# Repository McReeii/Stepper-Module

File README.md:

# Stepper-Module
 Smart_Stepper_Module

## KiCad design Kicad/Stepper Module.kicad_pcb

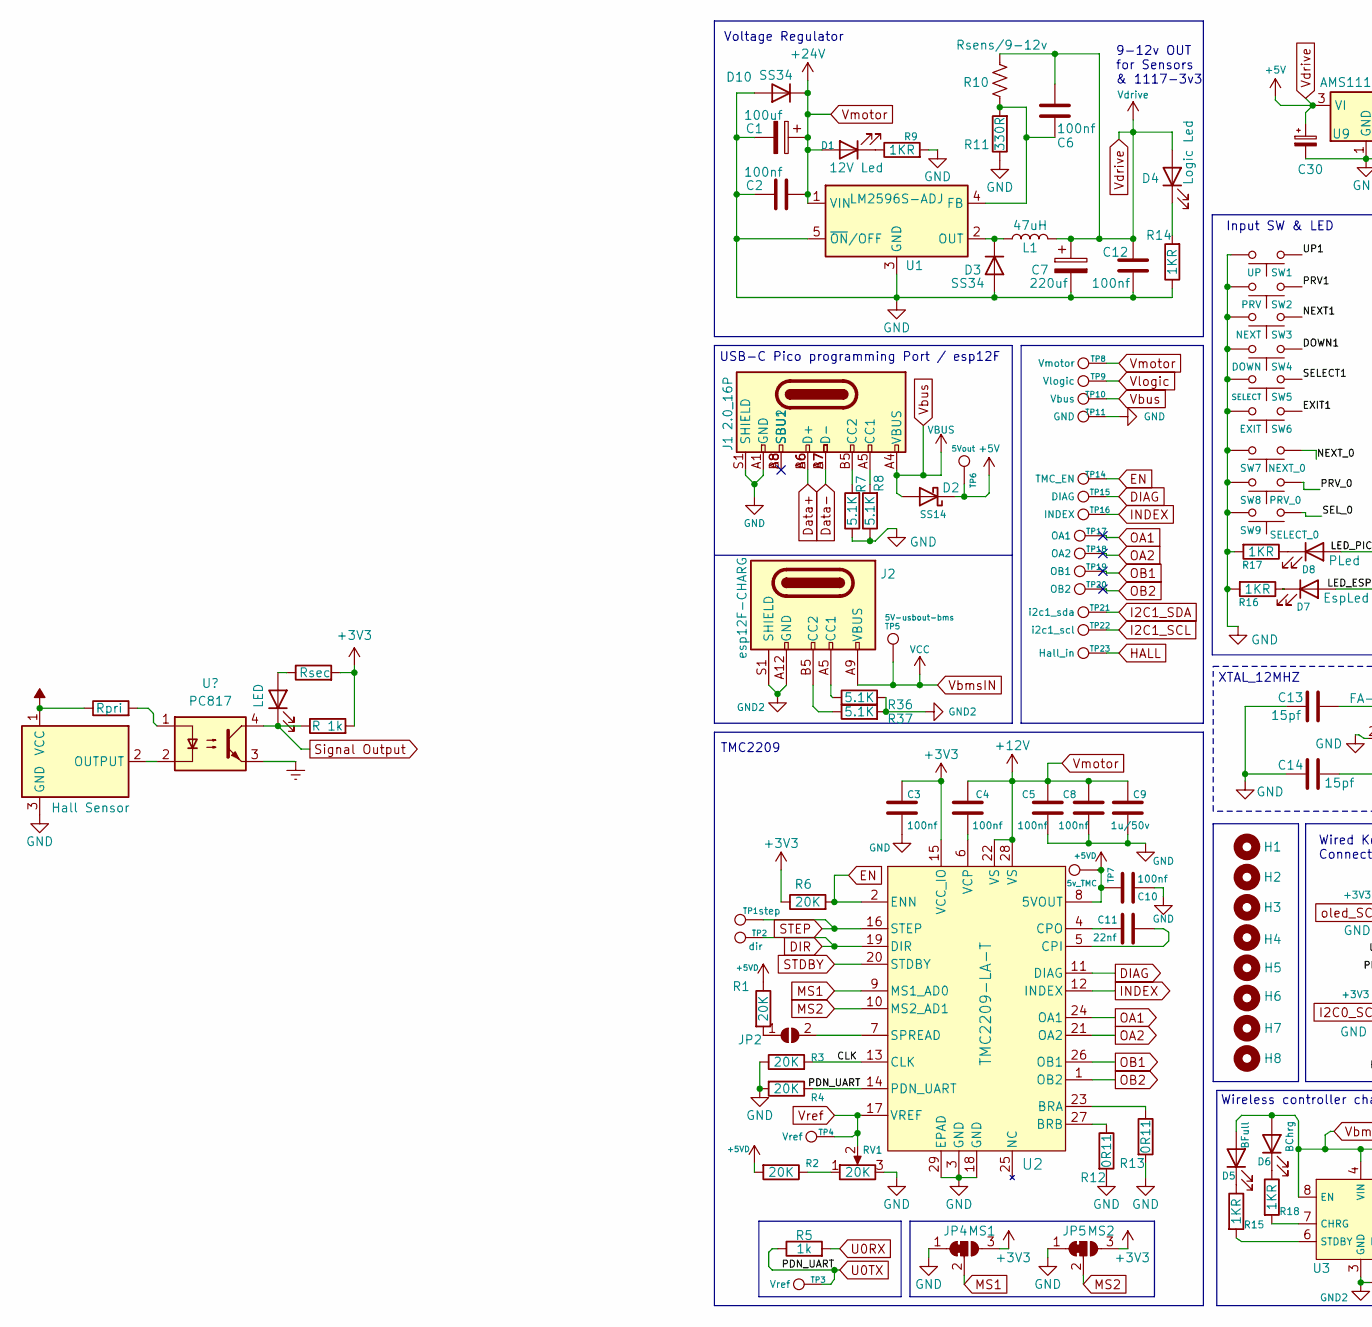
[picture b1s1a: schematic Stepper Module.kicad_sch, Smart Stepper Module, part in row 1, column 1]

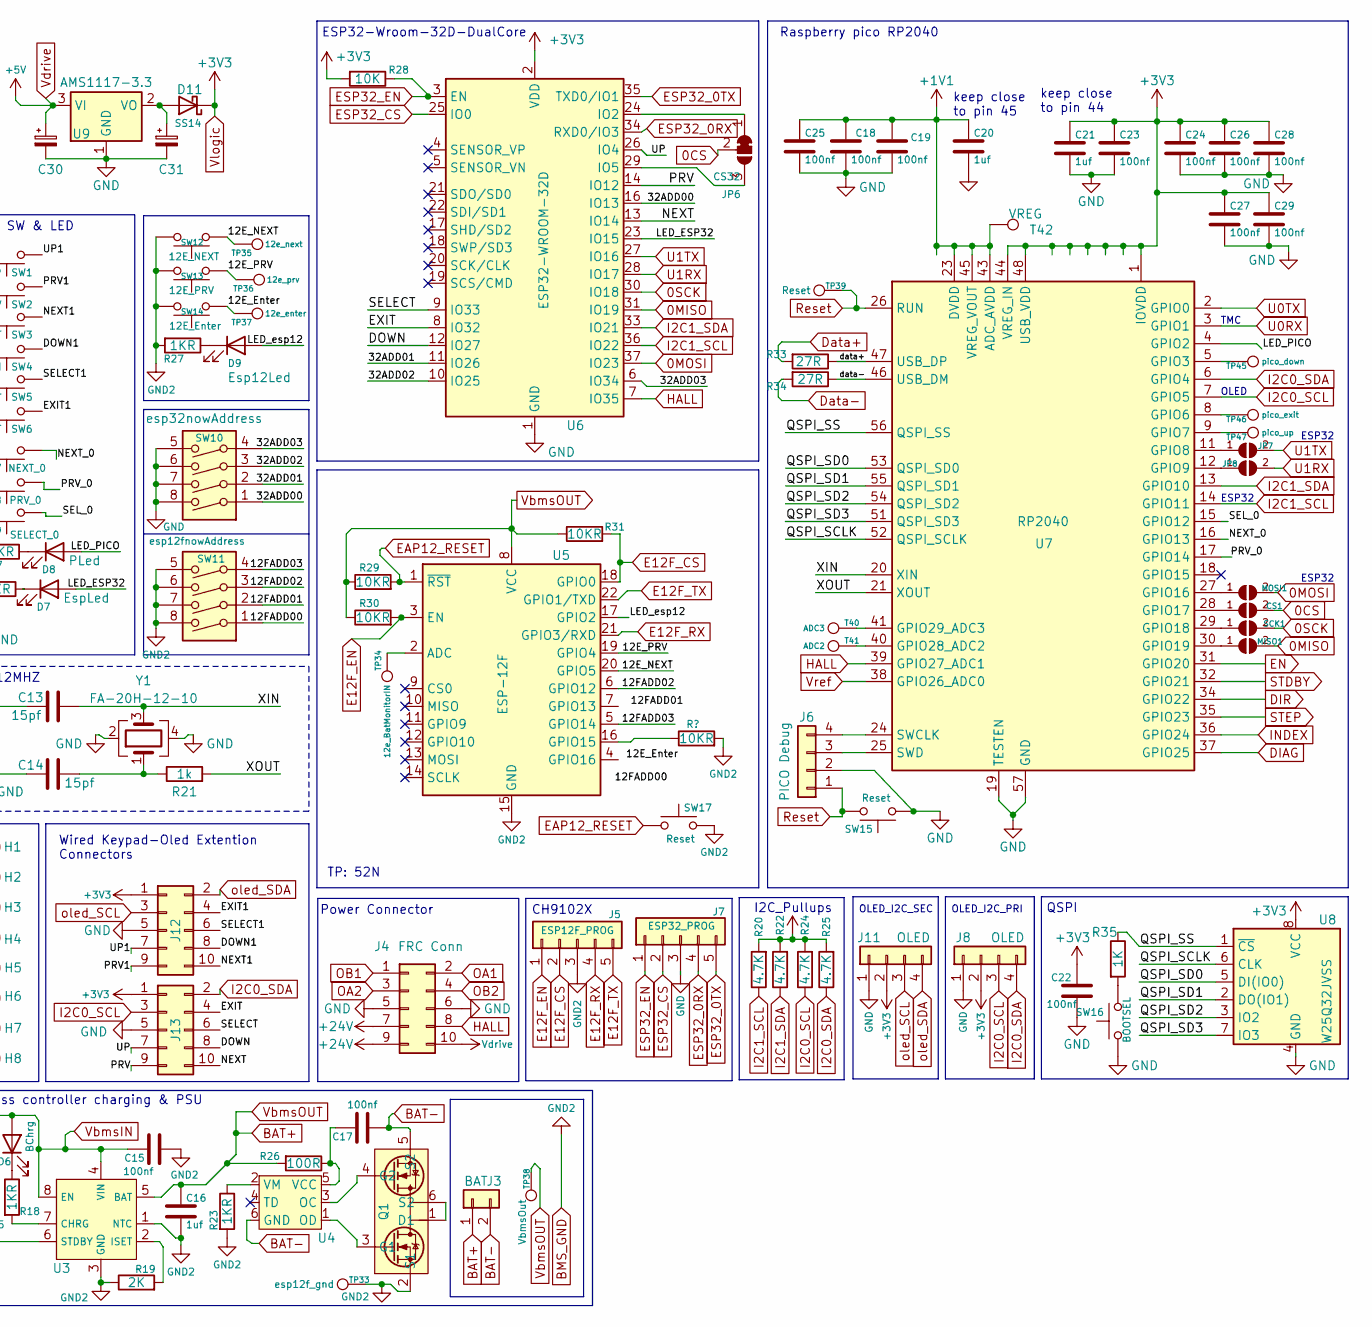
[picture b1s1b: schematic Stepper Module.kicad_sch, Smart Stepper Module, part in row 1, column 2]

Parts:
C1: 100uf; CP_Elec_8x11.9
C2, C3, C4, C5, C6, C8, C10, C12, C15, C17, C18, C19, C22, C23, C24, C25, C26, C27, C28, C29: 100nf; C_0603_1608Metric
C7: 220uf; CP_Elec_8x11.9
C9: 1u/50v; C_0805_2012Metric
C11: 22nf; C_0603_1608Metric
C13, C14: 15pf; C_1206_3216Metric
C16, C20, C21: 1uf; C_0805_2012Metric
C30, C31: C_Polarized_Small; CP_EIA-3528-21_Kemet-B
CS1: SolderJumper_2_Open; SolderJumper-2_P1.3mm_Open_TrianglePad1.0x1.5mm
D1: 12V Led; LED_1206_3216Metric
D2, D11: SS14; D_SMA
D3, D10: SS34; D_SMA
D4: Logic Led; LED_1206_3216Metric
D5: BFull; LED_1206_3216Metric
D6: BChrg; LED_1206_3216Metric
D7: EspLed; LED_1206_3216Metric
D8: PLed; LED_1206_3216Metric
D9: Esp12Led; LED_1206_3216Metric
H1, H2, H3, H4, H5, H6, H7, H8: MountingHole; MountingHole_5mm
J1: 2.0_16P; USB_C_Receptacle_GCT_USB4105-xx-A_16P_TopMnt_Horizontal
J2: esp12F-CHARG; USB_C_Receptacle_GCT_USB4125-xx-x_6P_TopMnt_Horizontal
J3: BAT; TestPoint_2Pads_Pitch2.54mm_Drill0.8mm
J4: FRC Conn; IDC-Header_2x05_P2.54mm_Vertical
J5: ESP12F_PROG; PinSocket_1x05_P1.27mm_Vertical_SMD_Pin1Left
J6: PICO Debug; PinSocket_1x04_P1.27mm_Vertical_SMD_Pin1Left
J7: ESP32_PROG; PinSocket_1x05_P1.27mm_Vertical_SMD_Pin1Left
J8: OLED; PinSocket_1x04_P2.54mm_Vertical_SMD_Pin1Right
J11: OLED; PinSocket_1x04_P2.54mm_Vertical
J12, J13: Conn_02x05_Odd_Even; PinSocket_2x05_P2.54mm_Vertical
JP2, JP7, JP8: SolderJumper_2_Open; SolderJumper-2_P1.3mm_Open_TrianglePad1.0x1.5mm
JP4: MS1; SolderJumper-3_P1.3mm_Bridged12_Pad1.0x1.5mm_NumberLabels
JP5: MS2; SolderJumper-3_P1.3mm_Bridged12_Pad1.0x1.5mm_NumberLabels
JP6: CS32; SolderJumper-3_P1.3mm_Bridged12_Pad1.0x1.5mm_NumberLabels
L1: 47uH; L_12x12mm_H8mm
MISO1: SolderJumper_2_Open; SolderJumper-2_P1.3mm_Open_TrianglePad1.0x1.5mm
MOSI1: SolderJumper_2_Open; SolderJumper-2_P1.3mm_Open_TrianglePad1.0x1.5mm
Q1: 8205N_TSSOP8_6PIN
R1, R2, R3, R4, R6: 20K; R_0603_1608Metric
R5, R21: 1k; R_0805_2012Metric
R7, R8, R36, R37: 5.1K; R_0805_2012Metric
R9, R14, R15, R16, R17, R18, R23, R27: 1KR; R_0805_2012Metric
R10: Rsens/9-12v; R_0805_2012Metric
R11: 330R; R_0805_2012Metric
R12, R13: 0R11; R_0805_2012Metric
R19: 2K; R_0805_2012Metric
R20, R22, R24, R25: 4.7K; R_0805_2012Metric
R26: 100R; R_0805_2012Metric
R28: 10K; R_0805_2012Metric
R29, R30, R31: 10KR; R_0805_2012Metric
R33, R34: 27R; R_0805_2012Metric
R35: 1K; R_0805_2012Metric
RV1: 20K; Potentiometer_Bourns_3214J_Horizontal
SCK1: SolderJumper_2_Open; SolderJumper-2_P1.3mm_Open_TrianglePad1.0x1.5mm
SW1: UP; SW_Push_1P1T_NO_CK_PTS125Sx43PSMTR
SW2: PRV; SW_Push_1P1T_NO_CK_PTS125Sx43PSMTR
SW3: NEXT; SW_Push_1P1T_NO_CK_PTS125Sx43PSMTR
SW4: DOWN; SW_Push_1P1T_NO_CK_PTS125Sx43PSMTR
SW5: SELECT; SW_Push_1P1T_NO_CK_PTS125Sx43PSMTR
SW6: EXIT; SW_Push_1P1T_NO_CK_PTS125Sx43PSMTR
SW7: NEXT_0; SW_Push_1P1T_XKB_TS-1187A
SW8: PRV_0; SW_Push_1P1T_XKB_TS-1187A
SW9: SELECT_0; SW_Push_1P1T_XKB_TS-1187A
SW10: esp32nowAddress; SMDIP-8_W11.48mm
SW11: esp12fnowAddress; SMDIP-8_W11.48mm
SW12: 12E_NEXT; SW_Push_1P1T_XKB_TS-1187A
SW13: 12E_PRV; SW_Push_1P1T_XKB_TS-1187A
SW14: 12E_Enter; SW_Push_1P1T_NO_CK_PTS125Sx43PSMTR
SW15, SW17: Reset; SW_Push_1P1T_XKB_TS-1187A
SW16: BOOTSEL; SW_Push_1P1T_XKB_TS-1187A
T40: ADC3; TestPoint_Pad_1.0x1.0mm
T41: ADC2; TestPoint_Pad_1.0x1.0mm
T42: VREG; TestPoint_Pad_1.0x1.0mm
TP1: step; TestPoint_Pad_1.0x1.0mm
TP2: dir; TestPoint_Pad_1.0x1.0mm
TP3, TP4: Vref; TestPoint_Pad_1.0x1.0mm
TP5: 5V-usbout-bms; TestPoint_Pad_1.0x1.0mm
TP6: 5Vout; TestPoint_Pad_1.0x1.0mm
TP7: 5v_TMC; TestPoint_Pad_1.0x1.0mm
TP8: Vmotor; TestPoint_Pad_1.0x1.0mm
TP9: Vlogic; TestPoint_Pad_1.0x1.0mm
TP10: Vbus; TestPoint_Pad_1.0x1.0mm
TP11: GND; TestPoint_Pad_1.0x1.0mm
TP14: TMC_EN; TestPoint_Pad_1.0x1.0mm
TP15: DIAG; TestPoint_Pad_1.0x1.0mm
TP16: INDEX; TestPoint_Pad_1.0x1.0mm
TP17: OA1; TestPoint_Pad_1.0x1.0mm
TP18: OA2; TestPoint_Pad_1.0x1.0mm
TP19: OB1; TestPoint_Pad_1.0x1.0mm
TP20: OB2; TestPoint_Pad_1.0x1.0mm
TP21: i2c1_sda; TestPoint_Pad_1.0x1.0mm
TP22: i2c1_scl; TestPoint_Pad_1.0x1.0mm
TP23: Hall_in; TestPoint_Pad_1.0x1.0mm
TP33: esp12f_gnd; TestPoint_Pad_1.0x1.0mm
TP34: 12e_BatMonitorIN; TestPoint_Pad_1.0x1.0mm
TP35: 12e_next; TestPoint_Pad_1.0x1.0mm
TP36: 12e_prv; TestPoint_Pad_1.0x1.0mm
TP37: 12e_enter; TestPoint_Pad_1.0x1.0mm
TP38: VbmsOut; TestPoint_Pad_1.0x1.0mm
TP39: Reset; TestPoint_Pad_1.0x1.0mm
TP45: pico_down; TestPoint_Pad_1.0x1.0mm
TP46: pico_exit; TestPoint_Pad_1.0x1.0mm
TP47: pico_up; TestPoint_Pad_1.0x1.0mm
U1: LM2596S-ADJ; TO-263-5_TabPin3
U2: TMC2209-LA-T; QFN-28-1EP_5x5mm_P0.5mm_EP3.75x3.75mm_ThermalVias
U3: HTSOP-8-1EP_3.9x4.9mm_P1.27mm_EP2.4x3.2mm
U4: SC-74-6_1.5x2.9mm_P0.95mm
U5: ESP-12F; ESP-12E
U6: ESP32-WROOM-32D
U7: RP2040; QFN-56-1EP_7x7mm_P0.4mm_EP3.2x3.2mm_ThermalVias
U8: W25Q32JVSS; SOIC-8_5.23x5.23mm_P1.27mm
U9: AMS1117-3.3; SOT-223-3_TabPin2
Y1: FA-20H-12-10; Crystal_SMD_Abracon_ABM10-4Pin_2.5x2.0mm

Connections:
0CS: CS1.2 (B), JP6.2 (C)
0MISO: MISO1.2 (B), U6.31 (IO19); also elsewhere on the board
0MOSI: MOSI1.2 (B), U6.37 (IO23); also elsewhere on the board
0SCK: SCK1.2 (B), U6.30 (IO18); also elsewhere on the board
+1V1: C18.1, C19.1, C20.1, C25.1, T42.1, U7.23 (DVDD), U7.43 (ADC_AVDD), U7.45 (VREG_VOUT), U7.50 (DVDD)
+5VD: C10.2, R1.1, R2.2, TP7.1, U2.8 (5VOUT)
/12E_Enter: SW14.1, TP37.1, U5.4 (GPIO16)
/12E_NEXT: SW12.1, TP35.1, U5.20 (GPIO5)
/12E_PRV: SW13.1, TP36.1, U5.19 (GPIO4)
/12FADD00: SW11.1, U5.16 (GPIO15)
/12FADD01: SW11.2, U5.7 (GPIO13)
/12FADD02: SW11.3, U5.6 (GPIO12)
/12FADD03: SW11.4, U5.5 (GPIO14)
/32ADD00: SW10.1, U6.16 (IO13); also elsewhere on the board
/32ADD01: SW10.2, U6.11 (IO26); also elsewhere on the board
/32ADD02: SW10.3, U6.10 (IO25); also elsewhere on the board
/32ADD03: SW10.4, U6.6 (IO34); also elsewhere on the board
/CLK: R3.2, U2.13 (CLK)
/DOWN: J13.8, U6.12 (IO27); also elsewhere on the board
/DOWN1: J12.8, SW4.1
/EXIT: J13.4, U6.8 (IO32); also elsewhere on the board
/EXIT1: J12.4, SW6.1
/LED_ESP32: D7.2 (A), U6.23 (IO15); also elsewhere on the board
/LED_PICO: D8.2 (A), U7.4 (GPIO2)
/LED_esp12: D9.2 (A), U5.17 (GPIO2)
/NEXT: J13.10, U6.13 (IO14); also elsewhere on the board
/NEXT1: J12.10, SW3.1
/NEXT_0: SW7.1, U7.16 (GPIO13)
/PRV: J13.9, U6.14 (IO12); also elsewhere on the board
/PRV1: J12.9, SW2.1
/PRV_0: SW8.1, U7.17 (GPIO14)
/QSPI_SCLK: U7.52 (QSPI_SCLK), U8.6 (CLK)
/QSPI_SD0: U7.53 (QSPI_SD0), U8.5 (DI(IO0))
/QSPI_SD1: U7.55 (QSPI_SD1), U8.2 (DO(IO1))
/QSPI_SD2: U7.54 (QSPI_SD2), U8.3 (IO2)
/QSPI_SD3: U7.51 (QSPI_SD3), U8.7 (IO3)
/QSPI_SS: R35.1, U7.56 (QSPI_SS), U8.1 (~CS)
/SELECT: J13.6, U6.9 (IO33); also elsewhere on the board
/SELECT1: J12.6, SW5.1
/SEL_0: SW9.1, U7.15 (GPIO12)
/UP: J13.7, U6.26 (IO4); also elsewhere on the board
/UP1: J12.7, SW1.1
/XIN: C13.2, U7.20 (XIN), Y1.3
/XOUT: R21.2, U7.21 (XOUT)
/data+: R33.1, U7.47 (USB_DP)
/data-: R34.1, U7.46 (USB_DM)
BAT+: C16.1, J3.1, R26.2, R29.1, R30.1, R31.1, TP38.1, U3.5 (BAT), U5.8 (VCC)
BAT-: C17.2, J3.2, Q1.5 (S2), U4.6 (GND)
BMS_GND: C15.2, C16.2, J2.A12 (GND), J2.B12 (GND), J2.S1 (SHIELD), J5.3, Q1.2 (S1), R19.1, R23.2, R27.2, R36.2, R37.2, SW11.5, SW11.6, SW11.7, SW11.8, SW12.2, SW13.2, SW14.2, SW17.2, TP33.1, U3.1 (NTC), U3.3 (GND), U5.15 (GND)
DIAG: TP15.1, U2.11 (DIAG), U7.37 (GPIO25)
DIR: TP2.1, U2.19 (DIR), U7.34 (GPIO22)
Data+: J1.A6 (D+), J1.B6 (D+), R33.2
Data-: J1.A7 (D-), J1.B7 (D-), R34.2
E12F_CS: J5.2, R31.2, U5.18 (GPIO0)
E12F_EN: J5.1, R30.2, U5.3 (EN)
E12F_RX: J5.4, U5.21 (GPIO3/RXD)
E12F_TX: J5.5, U5.22 (GPIO1/TXD)
EAP12_RESET: R29.2, SW17.1, U5.1 (~RST)
EN: R6.2, TP14.1, U2.2 (ENN), U7.31 (GPIO20)
ESP32_0RX: J7.4, U6.34 (RXD0/IO3); also elsewhere on the board
ESP32_0TX: J7.5, U6.35 (TXD0/IO1); also elsewhere on the board
ESP32_CS: J7.2, U6.25 (IO0); also elsewhere on the board
ESP32_EN: J7.1, R28.1, U6.3 (EN); also elsewhere on the board
GND: C1.2, C2.1, C3.2, C5.2, C7.2, C8.2, C9.2, C10.1, C12.1, C13.1, C14.1, C18.2, C19.2, C20.2, C21.2, C22.2, C23.2, C24.2, C25.2, C26.2, C27.2, C28.2, C29.2, C30.2, C31.2, D3.2 (A), D10.2 (A), J1.A1 (GND), J1.A12 (GND), J1.B1 (GND), J1.B12 (GND), J1.S1 (SHIELD), J4.5, J4.6, J6.2, J7.3, J8.1, J11.1, J12.5, J13.5, JP4.1 (A), JP5.1 (A), R3.1, R4.2, R7.1, R8.1, R9.2, R11.1, R12.2, R13.2, R14.1, R16.2, R17.2, RV1.3, SW1.2, SW2.2, SW3.2, SW4.2, SW5.2, SW6.2, SW7.2, SW8.2, SW9.2, SW10.5, SW10.6, SW10.7, SW10.8, SW15.1, SW16.1, TP11.1, U1.3 (GND), U1.5 (~ON/OFF), U2.3 (GND), U2.18 (GND), U2.29 (EPAD), U6.1 (GND), U6.15 (GND), U6.38 (GND), U6.39 (GND), U7.19 (TESTEN), U7.57 (GND), U8.4 (GND), U9.1 (GND), Y1.2, Y1.4; also elsewhere on the board
HALL: J4.8, TP23.1, U6.7 (IO35), U7.39 (GPIO27_ADC1); also elsewhere on the board
I2C0_SCL: J8.3, J13.3, R24.1, U7.7 (GPIO5)
I2C0_SDA: J8.4, J13.2, R25.1, U7.6 (GPIO4)
I2C1_SCL: R20.1, TP22.1, U6.36 (IO22), U7.14 (GPIO11); also elsewhere on the board
I2C1_SDA: R22.1, TP21.1, U6.33 (IO21), U7.13 (GPIO10); also elsewhere on the board
INDEX: TP16.1, U2.12 (INDEX), U7.36 (GPIO24)
MS1: JP4.2 (C), U2.9 (MS1_AD0)
MS2: JP5.2 (C), U2.10 (MS2_AD1)
unnamed: C14.2, R21.1, Y1.1
unnamed: CS1.1 (A), U7.28 (GPIO17)
unnamed: D1.1 (K), R9.1
unnamed: D3.1 (K), L1.1, U1.2 (OUT)
unnamed: D4.1 (K), R14.2
unnamed: D5.1 (K), R15.1
unnamed: D6.1 (K), R18.1
unnamed: D7.1 (K), R16.1
unnamed: D8.1 (K), R17.1
unnamed: D9.1 (K), R27.1
unnamed: C31.1, D11.2 (A), U9.2 (VO)
unnamed: J1.A5 (CC1), R8.2
unnamed: J1.B5 (CC2), R7.2
unnamed: J2.A5 (CC1), R36.1
unnamed: J2.B5 (CC2), R37.1
unnamed: J6.3, U7.25 (SWD)
unnamed: J6.4, U7.24 (SWCLK)
unnamed: JP2.1 (A), R1.2
unnamed: JP2.2 (B), U2.7 (SPREAD)
unnamed 91: JP6.1 (A), U6.24 (IO2); also elsewhere on the board
unnamed 92: JP6.3 (B), U6.29 (IO5); also elsewhere on the board
unnamed: JP7.1 (A), U7.11 (GPIO8)
unnamed: JP8.1 (A), U7.12 (GPIO9)
unnamed: MISO1.1 (A), U7.30 (GPIO19)
unnamed: MOSI1.1 (A), U7.27 (GPIO16)
unnamed: Q1.1 (D1), Q1.6 (S2)
unnamed: Q1.3 (G1), U4.1 (OD)
unnamed: Q1.4 (G2), U4.3 (OC)
unnamed: R2.1, RV1.1
unnamed: R35.2, SW16.2
unnamed: SCK1.1 (A), U7.29 (GPIO18)
unnamed: C6.1, R10.2, R11.2, U1.4 (FB)
unnamed: R13.1, U2.23 (BRA)
unnamed: R12.1, U2.27 (BRB)
unnamed: C11.1, U2.5 (CPI)
unnamed: C11.2, U2.4 (CPO)
unnamed: C4.1, U2.6 (VCP)
unnamed: R18.2, U3.7 (CHRG)
unnamed: R19.2, U3.2 (ISET)
unnamed: R15.2, U3.6 (STDBY)
unnamed: C17.1, R26.1, U4.5 (VCC)
unnamed: R23.1, U4.2 (VM)
unnamed: TP34.1, U5.2 (ADC)
unnamed: TP45.1, U7.5 (GPIO3)
unnamed: TP46.1, U7.8 (GPIO6)
unnamed: TP47.1, U7.9 (GPIO7)
unnamed: T41.1, U7.40 (GPIO28_ADC2)
unnamed: T40.1, U7.41 (GPIO29_ADC3)
OA1: J4.2, TP17.1, U2.24 (OA1)
OA2: J4.3, TP18.1, U2.21 (OA2)
OB1: J4.1, TP19.1, U2.26 (OB1)
OB2: J4.4, TP20.1, U2.1 (OB2)
Reset: J6.1, SW15.2, TP39.1, U7.26 (RUN)
STDBY: U2.20 (STDBY), U7.32 (GPIO21)
STEP: TP1.1, U2.16 (STEP), U7.35 (GPIO23)
U0RX: R5.2, U7.3 (GPIO1)
U0TX: R4.1, R5.1, TP3.1, U2.14 (PDN_UART), U7.2 (GPIO0)
U1RX: JP8.2 (B), U6.28 (IO17); also elsewhere on the board
U1TX: JP7.2 (B), U6.27 (IO16); also elsewhere on the board
VbmsIN: C15.1, D5.2 (A), D6.2 (A), J2.A9 (VBUS), J2.B9 (VBUS), TP5.1, U3.4 (VIN), U3.8 (EN)
Vbus: D2.2 (A), J1.A4 (VBUS), J1.A9 (VBUS), J1.B4 (VBUS), J1.B9 (VBUS), TP10.1
Vdrive: C6.2, C7.1, C12.2, C30.1, D2.1 (K), D4.2 (A), J4.10, L1.2, R10.1, TP6.1, U9.3 (VI)
Vlogic: C3.1, C21.1, C22.1, C23.1, C24.1, C26.1, C27.1, C28.1, C29.1, D11.1 (K), J8.2, J11.2, J12.1, J13.1, JP4.3 (B), JP5.3 (B), R6.1, R20.2, R22.2, R24.2, R25.2, R28.2, TP9.1, U2.15 (VCC_IO), U6.2 (VDD), U7.1 (IOVDD), U7.10 (IOVDD), U7.22 (IOVDD), U7.33 (IOVDD), U7.42 (IOVDD), U7.44 (VREG_IN), U7.48 (USB_VDD), U7.49 (IOVDD), U8.8 (VCC); also elsewhere on the board
Vmotor: C1.1, C2.2, C4.2, C5.1, C8.1, C9.1, D1.2 (A), D10.1 (K), J4.7, J4.9, TP8.1, U1.1 (VIN), U2.22 (VS), U2.28 (VS)
Vref: RV1.2, TP4.1, U2.17 (VREF), U7.38 (GPIO26_ADC0)
oled_SCL: J11.3, J12.3
oled_SDA: J11.4, J12.2

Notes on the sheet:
ESP32
Input SW & LED
OLED
I2C_Pullups
Voltage Regulator
OLED_I2C_PRI
TMC
USB-C Pico programming Port / esp12F
ESP32-Wroom-32D-DualCore
QSPI
TP: 52N
TMC2209
OLED_I2C_SEC
keep close to pin 45
Power Connector
keep close to pin 44
Wired Keypad-Oled Extention Connectors
CH9102X
XTAL_12MHZ
Wireless controller charging & PSU
9-12v OUT for Sensors & 1117-3v3
Raspberry pico RP2040

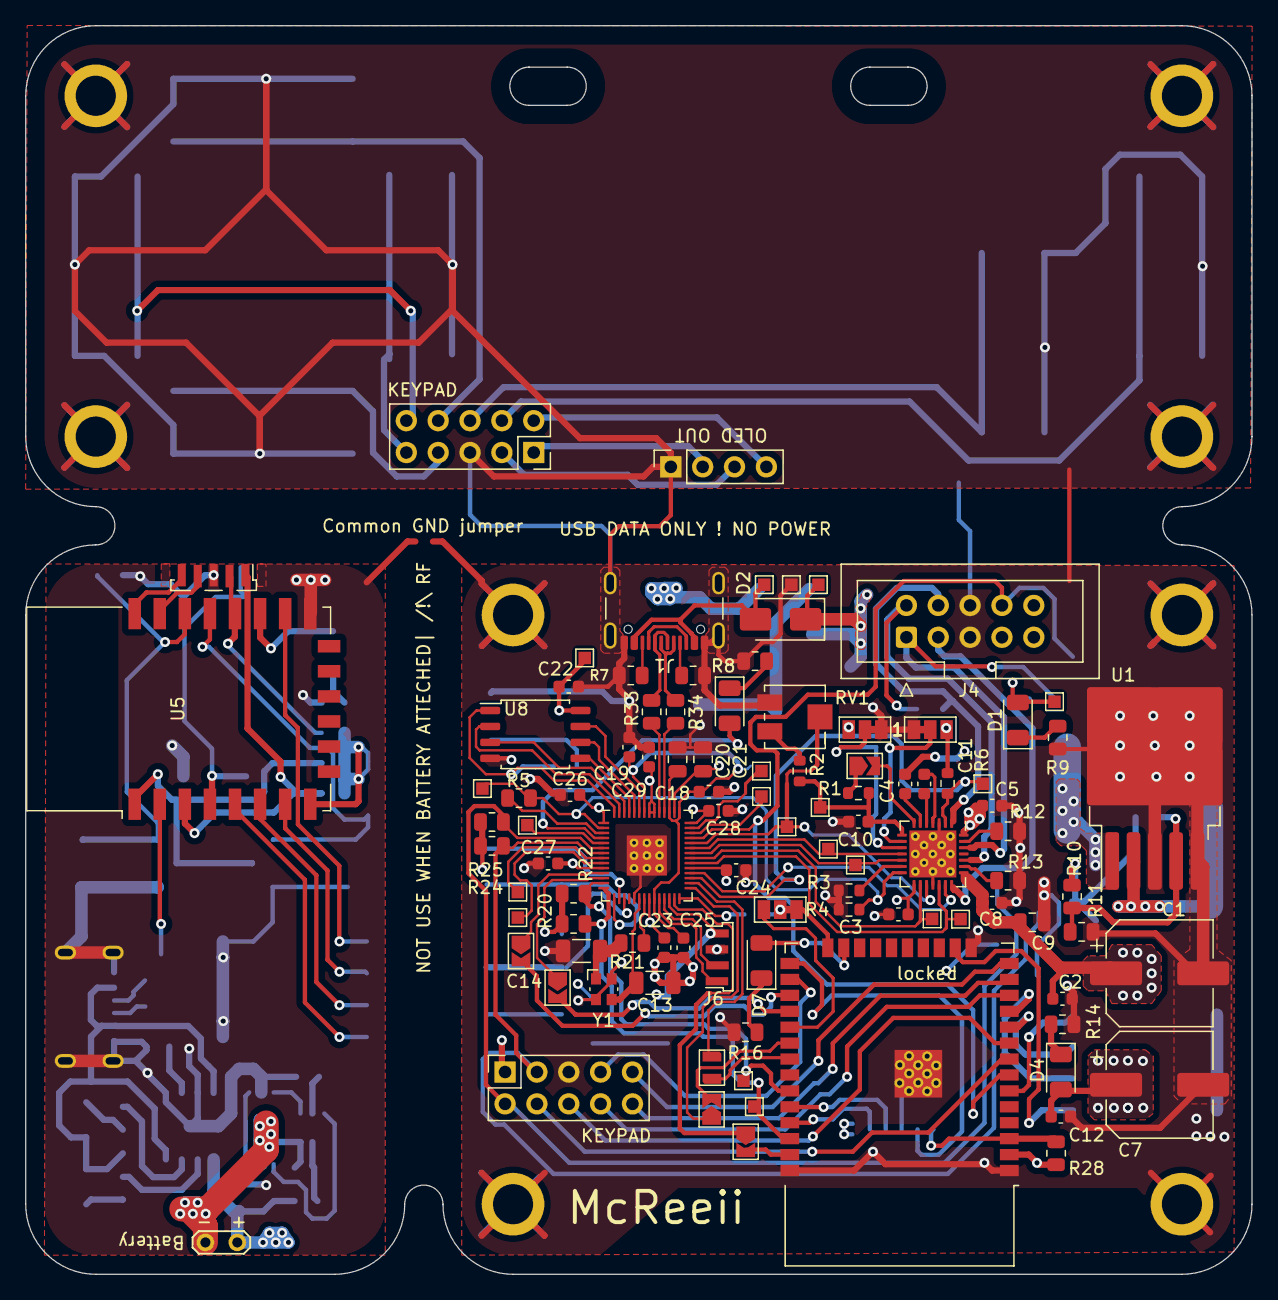
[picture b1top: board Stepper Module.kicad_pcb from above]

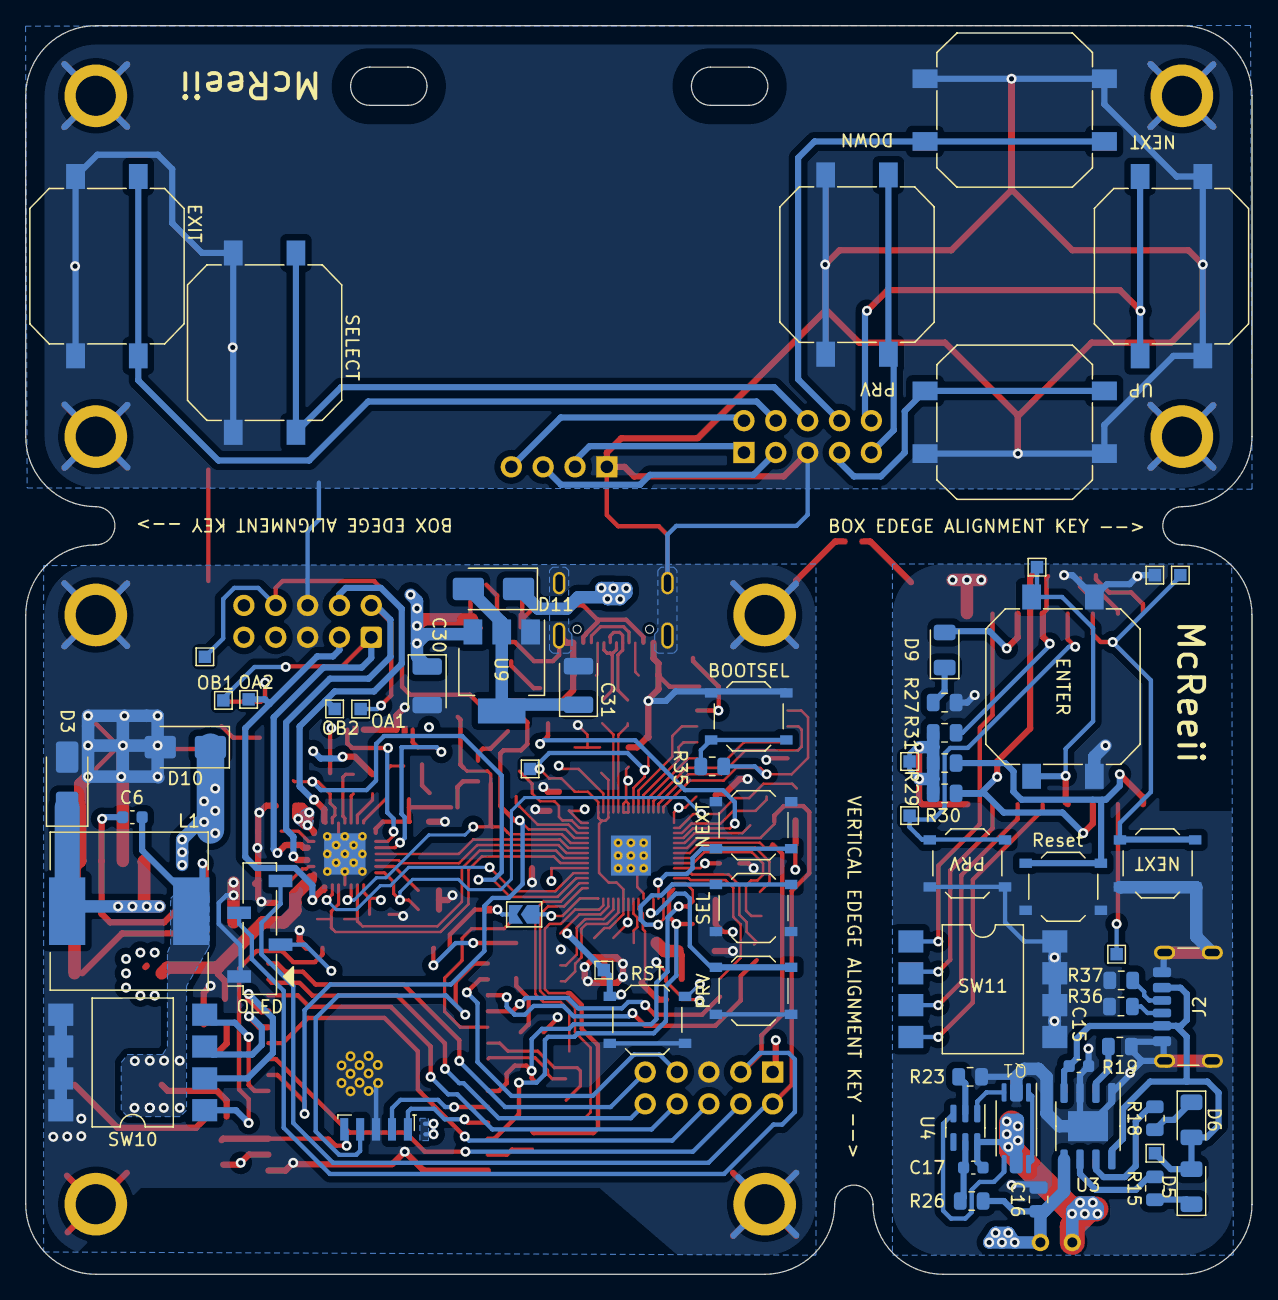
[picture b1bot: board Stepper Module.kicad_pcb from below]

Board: 4 copper layers, 97.8 x 99.6 mm, 171 parts (64 on the bottom side), 139 nets.

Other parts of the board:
locked: ESP32-WROOM-32D

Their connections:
0MISO: locked.31 (IO19); also elsewhere on the board
0MOSI: locked.37 (IO23); also elsewhere on the board
0SCK: locked.30 (IO18); also elsewhere on the board
/32ADD00: locked.16 (IO13); also elsewhere on the board
/32ADD01: locked.11 (IO26); also elsewhere on the board
/32ADD02: locked.10 (IO25); also elsewhere on the board
/32ADD03: locked.6 (IO34); also elsewhere on the board
/DOWN: locked.12 (IO27); also elsewhere on the board
/EXIT: locked.8 (IO32); also elsewhere on the board
/LED_ESP32: locked.23 (IO15); also elsewhere on the board
/NEXT: locked.13 (IO14); also elsewhere on the board
/PRV: locked.14 (IO12); also elsewhere on the board
/SELECT: locked.9 (IO33); also elsewhere on the board
/UP: locked.26 (IO4); also elsewhere on the board
ESP32_0RX: locked.34 (RXD0/IO3); also elsewhere on the board
ESP32_0TX: locked.35 (TXD0/IO1); also elsewhere on the board
ESP32_CS: locked.25 (IO0); also elsewhere on the board
ESP32_EN: locked.3 (EN); also elsewhere on the board
GND: locked.1 (GND), locked.15 (GND), locked.38 (GND), locked.39 (GND); also elsewhere on the board
HALL: locked.7 (IO35); also elsewhere on the board
I2C1_SCL: locked.36 (IO22); also elsewhere on the board
I2C1_SDA: locked.33 (IO21); also elsewhere on the board
unnamed 91: locked.24 (IO2); also elsewhere on the board
unnamed 92: locked.29 (IO5); also elsewhere on the board
U1RX: locked.28 (IO17); also elsewhere on the board
U1TX: locked.27 (IO16); also elsewhere on the board
Vlogic: locked.2 (VDD); also elsewhere on the board

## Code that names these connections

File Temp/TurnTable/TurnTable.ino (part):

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U8G2_SH1106_128X64_NONAME_F_HW_I2C u8g2(U8G2_R0, /* reset=*/ U8X8_PIN_NONE);

//------Stepper_PINS------
//#define PIN_INDEX          // Indexing
#define PIN_DIAG          25 // diagnostic
#define PIN_EN            20 // Enable (inverted) 
#define PIN_DIR           22 // direction
#define PIN_STEP          21 // Step
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
#define led               2
#define BUTTON_SELECT_PIN 15 // pin for Select Button
#define BUTTON_Exit_PIN   6 // pin for Exit button
#define BUTTON_FWD_PIN    13 // pin for NEXT button
#define BUTTON_DOWN_PIN   3 // pin for DOWN button
#define BUTTON_PRV_PIN    7 // pin for BACK button 
#define BUTTON_UP_PIN     14 // pin for UP button                                          

#define HALL_PIN          27 //Hall Sensor input (digital)
bool HomeNeeded = 1; 
//Input pin for the button, Button is active high, Disable internal pull-up resistor
//------Buttons_Config------
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  Serial.println("USB Serial: Connected");
  Serial.println("TMC Driver: Connected");
 
  pinMode(HALL_PIN, INPUT);
  pinMode(led, OUTPUT);
  pinMode(PIN_DIAG, INPUT);
  //pinMode(PIN_INDEX, INPUT);
  pinMode(PIN_EN, OUTPUT);
  pinMode(PIN_STEP, OUTPUT);
  pinMode(PIN_DIR, OUTPUT);
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  driver.semin(5);
  driver.semax(2);
  driver.sedn(0b01);
  driver.SGTHRS(STALL_VALUE); // Stallguard < threshold -> DIAG pin goes up

  stepper.setMaxSpeed(1000); // 3.6rev/s @ 6400steps/rev
  stepper.setAcceleration(2000); // 2000mm/s^2
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  stepper.enableOutputs();

  u8g2.setColorIndex(1);  // set the color to white
  u8g2.begin(); // not needed in this lib (/*Select=*/ BUTTON_SELECT_PIN, /*Right/Next=*/ BUTTON_NEXT_PIN, /*Left/Prev=*/ BUTTON_PRV_PIN, /*Up=*/ BUTTON_UP_PIN, /*Down=*/ BUTTON_DOWN_PIN, /*Home/Cancel=*/ BUTTON_Exit_PIN);
  u8g2.setBitmapMode(1);

  // define pins for buttons
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  // since it´s connected between some pin and GND
  pinMode(BUTTON_UP_PIN, INPUT_PULLUP); // up button
  pinMode(BUTTON_SELECT_PIN, INPUT_PULLUP); // select button
  pinMode(BUTTON_FWD_PIN, INPUT_PULLUP); // next button
  pinMode(BUTTON_PRV_PIN, INPUT_PULLUP); // prv button
  pinMode(BUTTON_DOWN_PIN, INPUT_PULLUP); // down button
  pinMode(BUTTON_Exit_PIN, INPUT_PULLUP);

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  u8g2.setCursor(0,32);
  u8g2.print("HALL: ");
  u8g2.setCursor(80,32);
  u8g2.print(digitalRead(HALL_PIN));
  u8g2.setCursor(110,32);
  u8g2.print("0");

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void Homming()
{
  int Home_sens = 0;
  int Hall_sens = digitalRead(HALL_PIN);
  if (HomeNeeded == 1){
    if (Hall_sens == 1){
      driver.shaft(TMC_dir);
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        item_selected = NUM_ITEMS-1;
      }
    }
    else if ((digitalRead(BUTTON_DOWN_PIN) == LOW) && (button_down_clicked == 0)) { // down button clicked - jump to next menu item
      item_selected = item_selected + 1; // select next item
      button_down_clicked = 1; // set button to clicked to only perform the action once
      if (item_selected >= NUM_ITEMS) { // last item was selected, jump to first menu item
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      u8g2.drawStr(25, 15+20+2, menu_items[item_selected]);   
      u8g2.drawXBMP( 4, 24, 16, 16, bitmap_icons[item_selected]);     

      // draw next item as icon + label
      u8g2.setFont(u8g_font_7x14);     
      u8g2.drawStr(25, 15+20+20+2+2, menu_items[item_sel_next]);   
      u8g2.drawXBMP( 4, 46, 16, 16, bitmap_icons[item_sel_next]);  
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
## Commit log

2024-07-03 files organized
2024-08-06 EspNOW
2024-08-06 PCB design Changes
2024-08-06 Pico Firmware added
2024-08-24 final send
2024-10-14 First update PCB V1
2024-10-14 Facet driver update
2026-05-29 Add library dependencies to redme.md
